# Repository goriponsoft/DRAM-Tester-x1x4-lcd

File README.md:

# DRAM Tester x1x4 lcd by Goripon Hardware

[日本語版 README はこちら](https://github.com/goriponsoft/Dram-Tester-x1x4-lcd/blob/main/README-ja.md)

 This is a stand-alone DRAM tester compatible with 4116/4164/41256/4532/4416/4464/44256 and equipped with an LCD. Although it is not a direct fork, it is created based on [zeus074/dramtester](https://github.com/zeus074/dramtester) and [cloudree/DRAM_Tester](https://github.com/cloudree/DRAM_Tester). Thanks to the two original authors. Both of the two references are under the GPL3.0 license, so this DRAM tester will also be released under the GPL3.0 license.

 This DRAM tester was created by Goripon Hardware (the hardware division of Doujin Circle Goripon Software).

 X(old Twitter): @goriponsoft

# Components
(Check schematic/bom.xlsx as it may not match the schematic updates)
|Part Number|Parts|Quantity|
|:--|:--|--:|
|C1-C4|Unpolarized capacitor 100nF (Withstand voltage 16V or more.)|4|
|C5,C8|Polarized capacitor 470uF (Withstand voltage 16V or more.)|2|
|C6,C7|Polarized capacitor 10uF (Withstand voltage 16V or more.)|2|
|IC1|DC-DC Converter(Charge pump), 8-Pin PDIP "TJ7660"|1|
|CN1|DC Power Connector, Jack "MJ-179PH"|1|
|JP1|Pin Header 1x3 and Jumper Pin|1|
|JP2|Pin Header 1x2 and Jumper Pin|1|
|LED1|LED, D3.0mm, Yellow (Forward voltage 2.1V)|1|
|LED2|LED, D3.0mm, Green or Red (Forward voltage 2.1V)|1|
|R1-R11,R19|Resistor 47 ohm, 1/4 watt, tolerance 5%|12|
|R12,R13|Resistor 47 ohm, 1/6 watt, tolerance 5%|2|
|R14,R17|Resistor 10K ohm, 1/4 watt, tolerance 5%|2|
|R15|Resistor 1.5K ohm, 1/4 watt, required low tolerance (ex. 1%)|1|
|R16|Resistor 750 ohm, 1/4 watt, required low tolerance (ex. 1%)|1|
|R18|Resistor 5.1K ohm, 1/4 watt, tolerance 5%|1|
|S0-S1|3M Zero pressure (ZIF) socket 16pin "216-3340-00-0602J"|2|
|S2|3M Zero pressure (ZIF) socket 18pin "218-3341-00-0602J"|1|
|S3|3M Zero pressure (ZIF) socket 20pin "220-3342-00-0602J"|1|
|SW1|6x6mm Through hole & ground terminal type tactile switch "DTS-63N-V"|1|
|SW2|Switch Slide ON None ON SPDT Top Slide Thru-Hole "SS12SDP2"|1|
|SW3|Switch Slide ON None ON DPDT Top Slide Thru-Hole "SS22SDP2"|1|
|U1|Arduino Nano|1|
|U2|MT3608 DCDC Module|1|
|U3|I2C OLED Screen 0.91in. 128x32dots|1|
|-|Pin header for module installation|-|
|-|9V-12V 1A Center+ ACDC adapter|1|

# Directory
- firmware: Firmware for Arduino Nano.
- firmware/ArduinoIDE/Dram-Tester-x1x4-lcd: Firmware source code for Arduino IDE environment. You can compile and write sketches using the Arduino IDE.
- firmware/ArduinoIDE/Dram-Tester-x1x4-lcd/build: Firmware compiled binary. You can write HEX files using AVR programmer.
- firmware/PlatformIO/Dram-Tester-x1x4-lcd: Firmware source code for PlatformIO environment. You can compile using PlatformIO and write compiled binaries.
- firmware/PlatformIO/Dram-Tester-x1x4-lcd/.pio/build/Arduino_nano: Firmware compiled binary. You can write HEX files using AVR programmer.
- schematic: Schematic data for KICAD7.
- schematic/production: Gerber data for PCB ordering.

# How to assemble
Refer to the photo of the finished product on this page and solder and place the components according to the silk screen printing on the board.

For the Arduino Nano, DCDC converter board, and OLED display, first solder the headers to the components, then insert the pin headers into the board and solder them. No other special steps are required, so follow the normal assembly method for electronic circuits.

# Preparation
*For the finished products and kits we distribute, steps 1 to 6 are not necessary because the firmware is already written.

1. Connect the power supply to the board (USB connector or DC jack), turn on the main power switch, and measure the 3.3V power output of the Arduino Nano with a voltage tester and make a note of it.
2. Change "#if 0" to "#if 1" near the beginning of the setup() function in Dram-Tester-x1x4-lcd.cpp (or Dram-Tester-x1x4-lcd.ino), and replace the "3.300" part of the equation that assigns a value to the calibrationValue variable with the voltage you noted down (if you don't mind the error, you can leave it as 3.300, but the voltage check may not work correctly).
3. Connect the Arduino Nano to the PC via USB, and write the compiled sketch using the Arduino IDE, or write the HEX file using PlatformIO or an AVR writer.
4. Turn the main power switch on and off on the board, or press the reset button to start the firmware (the modified firmware will run and the voltage correction value will be written to the EEPROM).
5. Change "#if 1" in the source back to "#if 0". Note that steps 1 to 5 only need to be done the first time, and are not necessary thereafter.
6. Write the compiled sketch again using the Arduino IDE, or write the HEX file using PlatformIO or AVR writer.
7. Turn on the main power switch on the board, then turn the tri-pot resistor of the MT3608DCDC converter module while measuring the voltage with a tester to adjust it to 12V. You can also press and hold the SELECT/ENTER button while turning on or resetting the power switch to enter the setting change mode and display the voltage.
8. Set the jumper pin of JP1 (socket power LED operation). When 1-2 is shorted, the light turns on when ON, when 2-3 is shorted, the light turns on when OFF, and when the jumper pin is removed, the light turns off all the time.

# How it works
0. Connect the ACDC adapter (center positive, 9V to 12V, 1A) to the DC jack. Although it can be operated by connecting a 5V power supply or PC to the Arduino nano's USB connector, we recommend using an ACDC adapter.
1. Turn off socket power switch, then insert DRAM under test into the socket. Insert into SOCKET0 for 4116, SOCKET1 for 4164/41256/4532, SOCKET2 for 4416/4464, and SOCKET3 for 44256. *Please note that if you insert a DRAM other than 4116 type into SOCKET0, it will be damaged.
2. Turn on socket power switch, check the LCD display, and select DRAM model number by pressing SELECT/ENTER button. The socket into which the DRAM should be inserted will also be displayed on the LCD, so check that it is correct.
3. Press and hold the SELECT/ENTER button to start the test. *For safety reasons, the buttons cannot be operated while the socket power switch is off.
4. After waiting a few tens of seconds to a few minutes (depending on the amount of DRAM and test stringency settings, less if an error occurs), the results will be displayed.
5. Turn off the socket power switch and remove the tested DRAM from the socket. If you want to replace it with another DRAM after testing, please turn off the socket power switch first.

# Setting change
By holding down the SELECT/ENTER button and turning on the main power switch, you can start up in setting change mode. As with normal DRAM model selection, short press the SELECT/ENTER button to select an item, long press to confirm or change settings.

- 4bit DRAM Test: Select whether to test 4bit DRAM with priority given to speed ("Speedy") or strictly ("Strict").
- Power5V Voltage: Check the voltage of the 5V power supply and select whether to abort the test ("Check") or ignore it and continue the test ("Ignore") if the voltage is abnormal. In the case of USB power, the voltage of the power supply may drop and the test may not be performed correctly.
- Erase EEPROM: You can initialize the settings by erasing the contents of the EEPROM (values for correction, etc. remain). When erasing is complete, you will be forced to exit the settings change mode.
- View Power12V: Displays voltage of 12V power supply and voltage error. If 12V power supply voltage is not appropriate, the 4116 DRAM cannot be tested. Please reset when exiting. *Voltage cannot be displayed if the socket power is turned off.
- View Button & Power5V: Displays button test and 5V power status. Please reset when exiting.
- Save and Exit: Save the changes, exit setting change mode, and proceed to normal DRAM model number selection. Changes will not be saved unless you exit setting change mode. If you do not want to save, you can avoid saving by resetting without making a decision with this item.

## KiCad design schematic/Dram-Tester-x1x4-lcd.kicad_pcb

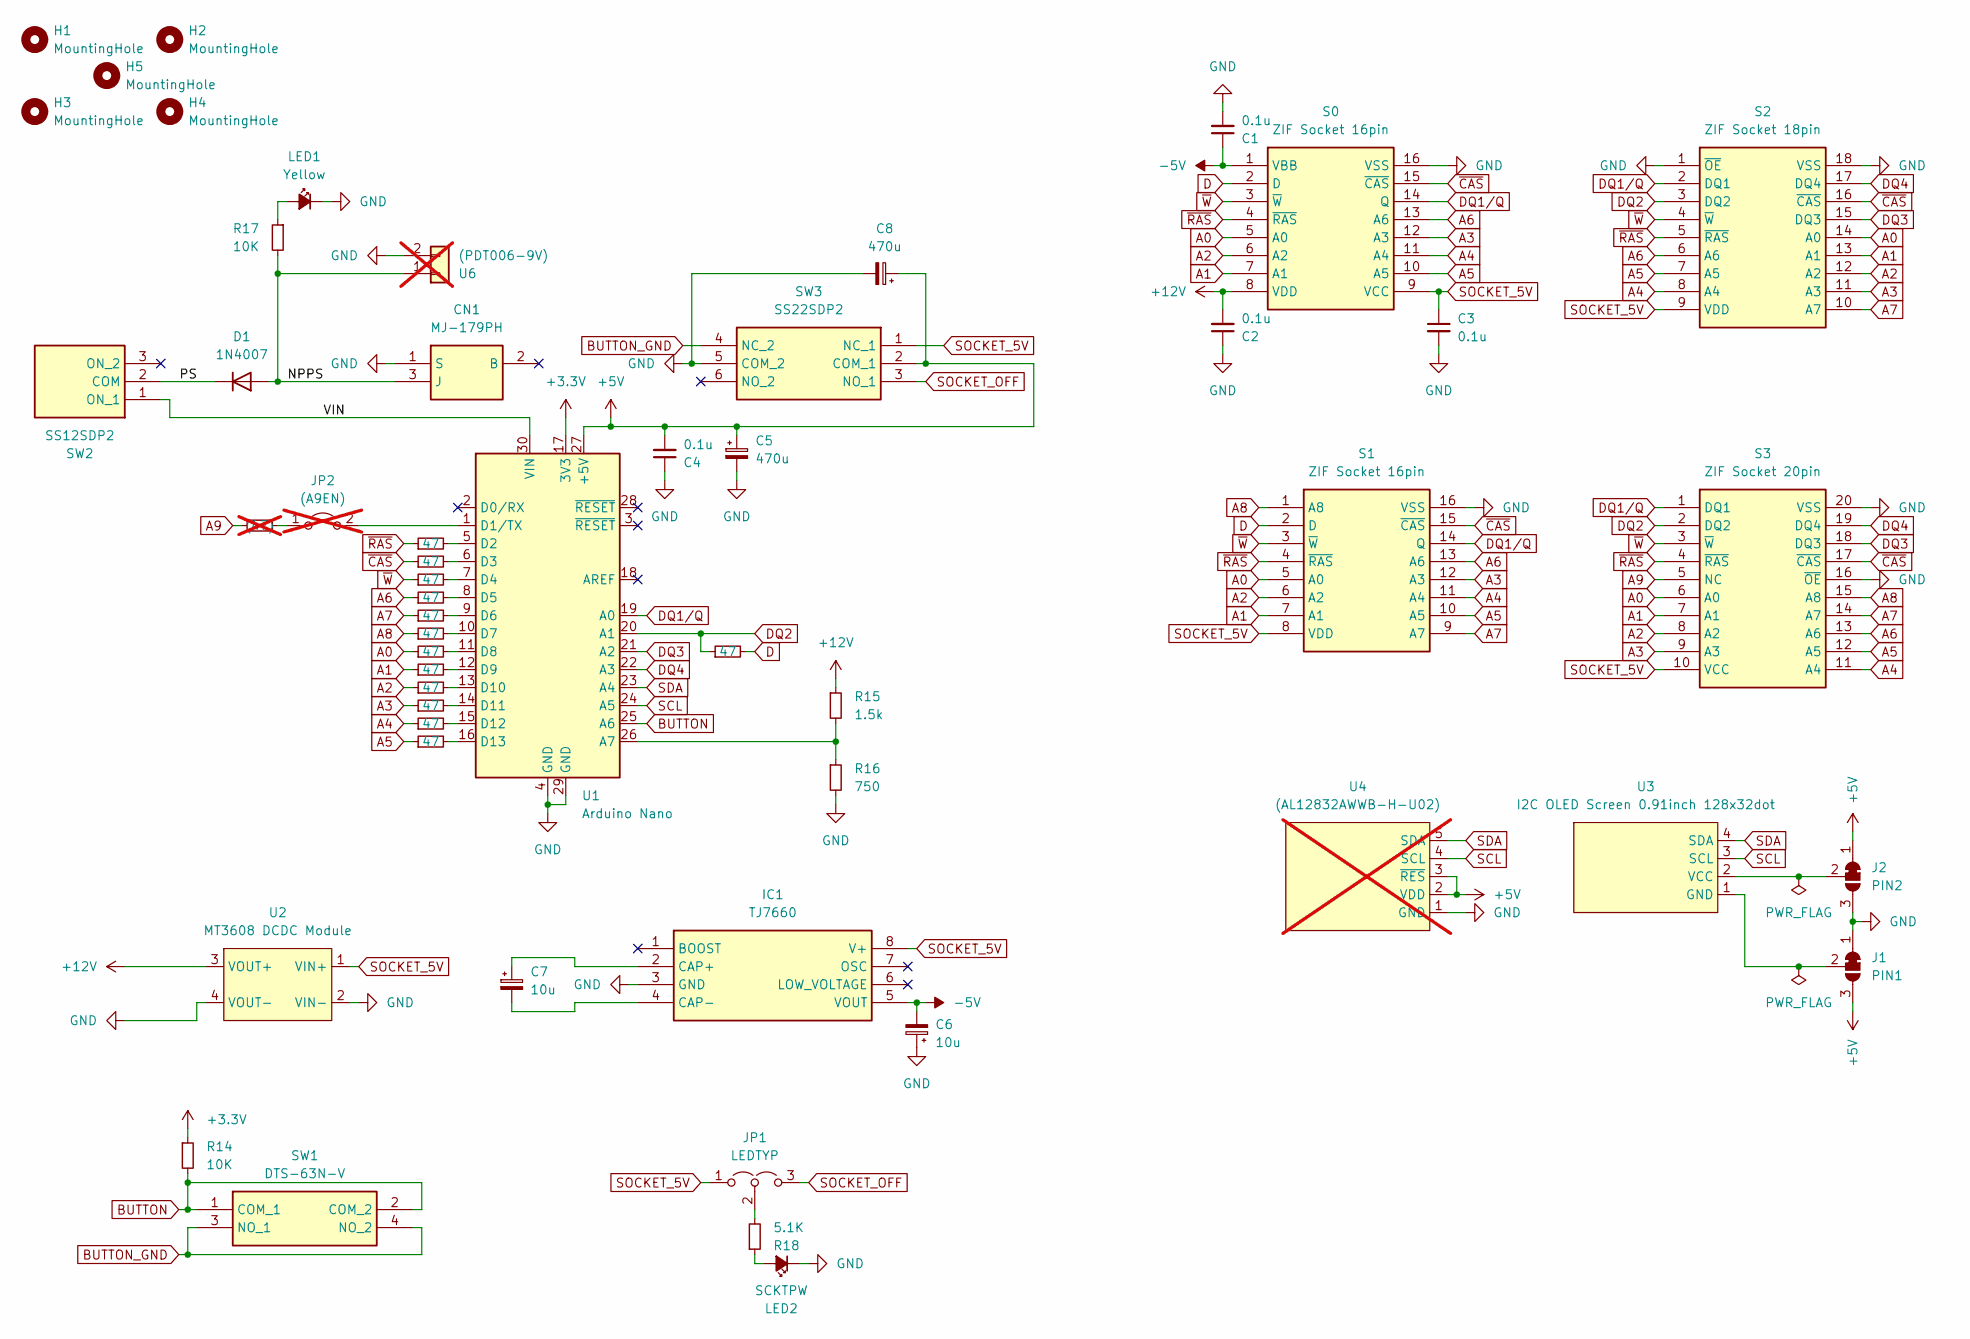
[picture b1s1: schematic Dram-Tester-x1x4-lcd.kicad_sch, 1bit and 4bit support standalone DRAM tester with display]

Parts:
C1, C2, C3, C4: 0.1u; C_Disc_D3.4mm_W2.1mm_P2.50mm
C5, C8: 470u; CP_Radial_D8.0mm_P3.50mm
C6, C7: 10u; CP_Radial_D5.0mm_P2.00mm
CN1: MJ-179PH; MJ179PH; Manufacturer_Part_Number MJ-179PH
D1: 1N4007; D_DO-41_SOD81_P10.16mm_Horizontal
H1, H2, H3, H4, H5: MountingHole; MountingHole_3.2mm_M3
IC1: TJ7660; DIP8_300mil_FineLongPad; Manufacturer_Part_Number TC7660SCPA; Mouser Part Number 579-TC7660SCPA
J1: PIN1; SolderJumper-3_P1.3mm_Bridged12_RoundedPad1.0x1.5mm
J2: PIN2; SolderJumper-3_P1.3mm_Bridged12_RoundedPad1.0x1.5mm
JP1: LEDTYP; PinHeader_1x03_P2.54mm_Vertical
JP2: (A9EN); PinHeader_1x02_P2.54mm_Vertical; not fitted
LED1: Yellow; LED_D3.0mm
LED2: SCKTPW; LED_D3.0mm
R1, R2, R3, R4, R5, R6, R7, R8, R9, R10, R11, R12, R13: 47; R_Axial_DIN0207_L6.3mm_D2.5mm_P7.62mm_Horizontal
R14, R17: 10K; R_Axial_DIN0207_L6.3mm_D2.5mm_P7.62mm_Horizontal
R15: 1.5k; R_Axial_DIN0207_L6.3mm_D2.5mm_P7.62mm_Horizontal
R16: 750; R_Axial_DIN0207_L6.3mm_D2.5mm_P7.62mm_Horizontal
R18: 5.1K; R_Axial_DIN0207_L6.3mm_D2.5mm_P7.62mm_Horizontal
R19: (47); R_Axial_DIN0207_L6.3mm_D2.5mm_P7.62mm_Horizontal; not fitted
S0, S1: ZIF Socket 16pin; DIP_Socket-16_W4.3_W5.08_W7.62_W10.16_W10.9_3M_216-3340-00-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
S2: ZIF Socket 18pin; DIP_Socket-18_W4.3_W5.08_W7.62_W10.16_W10.9_3M_218-3341-00-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
S3: ZIF Socket 20pin; DIP_Socket-20_W4.3_W5.08_W7.62_W10.16_W10.9_3M_220-3342-00-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
SW1: DTS-63N-V; DTS63NV; Manufacturer_Part_Number DTS-63N-V; Mouser Part Number 113-DTS-63N-V
SW2: SS12SDP2; Manufacturer_Part_Number SS12SDP2; Mouser Part Number 633-SS12SDP2
SW3: SS22SDP2; Manufacturer_Part_Number SS22SDP2; Mouser Part Number 633-SS22SDP2
U1: Arduino Nano; Arduino_Nano
U2: MT3608 DCDC Module; MT3608_DCDC_Module
U3: I2C OLED Screen 0.91inch 128x32dot; I2C_OLED_0.91in_128x32
U4: (AL12832AWWB-H-U02); AL12832AWWB-H-U02; not fitted
U6: (PDT006-9V); PinHeader_1x02_P2.54mm_Vertical; not fitted

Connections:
+3.3V: R14.1, U1.17 (3V3)
+5V: C4.2, C5.1, C8.1, J1.3 (B), J2.1 (A), SW3.2 (COM_1), U1.27 (+5V), U4.2 (VDD), U4.3 (~RES)
+12V: C2.2, R15.1, S0.8 (VDD), U2.3 (VOUT+)
-5V: C1.1, C6.2, IC1.5 (VOUT), S0.1 (VBB)
/NPPS: CN1.3 (J), D1.2 (A), R17.2, U6.1
/PS: D1.1 (K), SW2.2 (COM)
/VIN: SW2.1 (ON_1), U1.30 (VIN)
A0: R7.1, S0.5 (A0), S1.5 (A0), S2.14 (A0), S3.6 (A0)
A1: R8.1, S0.7 (A1), S1.7 (A1), S2.13 (A1), S3.7 (A1)
A2: R9.1, S0.6 (A2), S1.6 (A2), S2.12 (A2), S3.8 (A2)
A3: R10.1, S0.12 (A3), S1.12 (A3), S2.11 (A3), S3.9 (A3)
A4: R11.1, S0.11 (A4), S1.11 (A4), S2.8 (A4), S3.11 (A4)
A5: R12.1, S0.10 (A5), S1.10 (A5), S2.7 (A5), S3.12 (A5)
A6: R4.1, S0.13 (A6), S1.13 (A6), S2.6 (A6), S3.13 (A6)
A7: R5.1, S1.9 (A7), S2.10 (A7), S3.14 (A7)
A8: R6.1, S1.1 (A8), S3.15 (A8)
A9: R19.1, S3.5 (NC)
BUTTON: R14.2, SW1.1 (COM_1), SW1.2 (COM_2), U1.25 (A6)
BUTTON_GND: SW1.3 (NO_1), SW1.4 (NO_2), SW3.4 (NC_2)
D: R13.2, S0.2 (D), S1.2 (D)
DQ1/Q: S0.14 (Q), S1.14 (Q), S2.2 (DQ1), S3.1 (DQ1), U1.19 (A0)
DQ2: R13.1, S2.3 (DQ2), S3.2 (DQ2), U1.20 (A1)
DQ3: S2.15 (DQ3), S3.18 (DQ3), U1.21 (A2)
DQ4: S2.17 (DQ4), S3.19 (DQ4), U1.22 (A3)
GND: C1.2, C2.1, C3.2, C4.1, C5.2, C6.1, C8.2, CN1.1 (S), IC1.3 (GND), J1.1 (A), J2.3 (B), LED1.1 (K), LED2.1 (K), R16.2, S0.16 (VSS), S1.16 (VSS), S2.1 (~OE), S2.18 (VSS), S3.16 (~OE), S3.20 (VSS), SW3.5 (COM_2), U1.4 (GND), U1.29 (GND), U2.2 (VIN-), U2.4 (VOUT-), U4.1 (GND), U6.2
unnamed: C7.1, IC1.2 (CAP+)
unnamed: C7.2, IC1.4 (CAP-)
unnamed: J1.2 (C), U3.1 (GND)
unnamed: J2.2 (C), U3.2 (VCC)
unnamed: JP1.2 (C), R18.2
unnamed: JP2.1 (A), R19.2
unnamed: JP2.2 (B), U1.1 (D1/TX)
unnamed: LED1.2 (A), R17.1
unnamed: LED2.2 (A), R18.1
unnamed: R15.2, R16.1, U1.26 (A7)
unnamed: R1.2, U1.5 (D2)
unnamed: R2.2, U1.6 (D3)
unnamed: R3.2, U1.7 (D4)
unnamed: R4.2, U1.8 (D5)
unnamed: R5.2, U1.9 (D6)
unnamed: R6.2, U1.10 (D7)
unnamed: R7.2, U1.11 (D8)
unnamed: R8.2, U1.12 (D9)
unnamed: R9.2, U1.13 (D10)
unnamed: R10.2, U1.14 (D11)
unnamed: R11.2, U1.15 (D12)
unnamed: R12.2, U1.16 (D13)
SCL: U1.24 (A5), U3.3 (SCL), U4.4 (SCL)
SDA: U1.23 (A4), U3.4 (SDA), U4.5 (SDA)
SOCKET_5V: C3.1, IC1.8 (V+), JP1.1 (A), S0.9 (VCC), S1.8 (VDD), S2.9 (VDD), S3.10 (VCC), SW3.1 (NC_1), U2.1 (VIN+)
SOCKET_OFF: JP1.3 (B), SW3.3 (NO_1)
~CAS: R2.1, S0.15 (~CAS), S1.15 (~CAS), S2.16 (~CAS), S3.17 (~CAS)
~RAS: R1.1, S0.4 (~RAS), S1.4 (~RAS), S2.5 (~RAS), S3.4 (~RAS)
~W: R3.1, S0.3 (~W), S1.3 (~W), S2.4 (~W), S3.3 (~W)

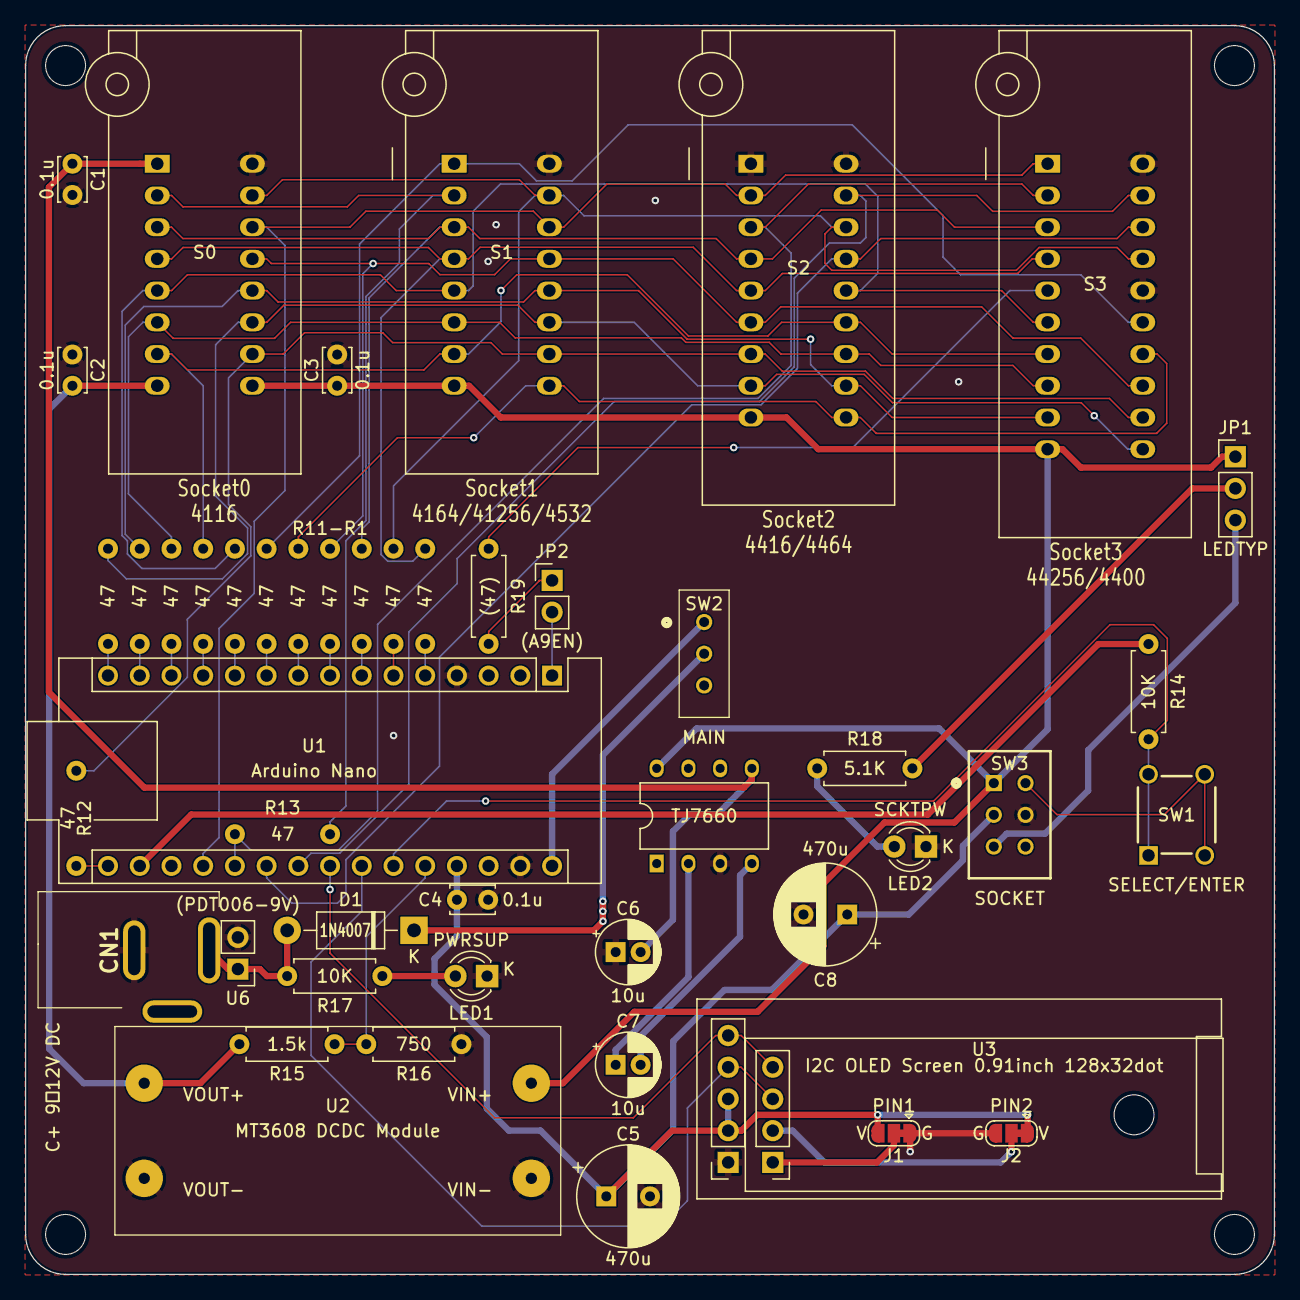
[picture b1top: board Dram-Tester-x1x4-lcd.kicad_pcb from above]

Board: 2 copper layers, 100.0 x 100.0 mm, 53 parts (0 on the bottom side), 54 nets.

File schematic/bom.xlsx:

Dram-Tester-x1x4-lcd BOM
 | Ref# | Detail | Value | Qnty
 | C1-C4 | MLC capacitor or Ceramic capacitor, radial lead, lead pitch 2.5mm | 0.1uF(100nF) 50V | 4
 | C5, C8 | ALUM capacitor, radial lead, lead pitch 3.5mm | 470uF 16V | 2
 | C6, C7 | ALUM capacitor, radial lead, lead pitch 2.0mm | 10uF 16V | 2
 | CN1 | DC jack | MJ-179PH | 1
 | D1 | General Purpose Rectifier Diode, DO-41 | 1N4007 | 1
 | IC1 | Super Charge Pump DC-to-DC Voltage Converter, DIP | TJ7660 | 1
 | JP1 | Pin Header 1x3 | - | 1
 | JP2 | Pin Header 1x2 | - | 1
 | LED1 | LED, D3.0mm, Yellow | OSY5JA3Z74A | 1
 | LED2 | LED, D3.0mm, Green | OSG5TA3Z74A | 1
 | R1-R13 | Register 1/4W, tolerance 5% | 47 ohm | 13
 | R19 | Register 1/4W, tolerance 5% | 47 ohm | 1
 | R14, R17 | Register 1/4W, tolerance 5% | 10K ohm | 2
 | R15 | Register 1/4W, low tolerance | 1.5K ohm | 1
 | R16 | Register 1/4W, low tolerance | 750 ohm | 1
 | R18 | Register 1/4W, tolerance 5% | 5.1K ohm | 1
 | S0-S1 | Zero pressure (ZIF) socket 16pin | 216-3340-00-0602J | 2
 | S2 | Zero pressure (ZIF) socket 18pin | 218-3341-00-0602J | 1
 | S3 | Zero pressure (ZIF) socket 20pin | 220-3342-00-0602J | 1
 | SW1 | 6x6mm tactile switch, through hole | DTS-63N-V | 1
 | SW2 | Slide switch, through hole, SPDT ON-ON | SS12SDP2 | 1
 | SW3 | Slide switch, through hole, DPDT ON-ON | SS22SDP2 | 1
 | U1 | Arduino Nano | - | 1
 | U2 | MT3608 DC-DC converter module | - | 1
 | U3 | OLED Screen 0.91inch, I2C SSD1306 controller, 128x32 dot | - | 1

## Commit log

2024-03-16 First Release
    First release distribution version.
2024-03-16 Modify README
    Modify README
    Fixed incorrect line breaks
2024-03-16 Modified README
    Modified README
    README.md and README-ja.md were formatted as markdown files.
2024-03-16 Modified README
    Modified README
    Add forward voltage to LED in BOM & parts list.
2024-03-24 Modified README
    Modified README
    ACDC adapter voltage correction and 12V voltage display note added.
2025-03-15 Added support for MB8265A type DRAM
    MB8265A(1ピンが負論理のREFRESH信号である)タイプのDRAMのサポートを追加。
    Added support for MB8265A (pin 1 is a negative logic refresh signal) type DRAM.
2025-03-23 Schematic modified
    回路図を修正
    Schematic modified.
    積層セラミックコンデンサのピッチを2.5mmに変更
    Changed pitch of MLCC to 2.5 mm.
    未実装の5V-DCDCモジュールを削除
    Remove unmounted 5V-DCDC module
2025-03-23 README.md modified
    README.mdを修正
    README.md modified.
    部品表が更新されていなかったため更新
    Updated the parts list because it had not been updated.
2025-03-23 README.md modified.
    README.mdを修正
    README.md modified.
    部品表が正しく更新されていなかったため再更新
    The parts list was not updated correctly so it was updated again.
2025-04-22 Modified README
    READMEに完成品の写真を貼り付けた
    I've attached a photo of the finished product in the README.
    READMEに組み立て方の項目を追加した
    Added assembly instructions to the README.
2025-04-28 Modified README
    READMEの準備の項目に電圧補正値の書き込み手順を追加しました
    Added instructions for writing voltage compensation values ​​to the preparation section of the README.
2025-04-28 Modified README
    ACアダプタの出力電流値が1A必要である旨を追記
    Added that the ACDC adapter requires an output current of 1A.
2025-04-29 Modified README
    細かな文言の修正
    Minor wording corrections.
2025-06-06 Modified Schematic & README
    Modified Schematic & README
    回路図および基板のリビジョンを4に更新し部品番号のシルク印刷の欠落を修正
    Updated schematic and PCB revision to 4 and fixed missing part number silkscreen.
    READMEの準備項に頒布品に関する記載を追加
    Added information about distribution items to the preparation section of the README.
